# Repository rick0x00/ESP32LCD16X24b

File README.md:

# ESP32 LCD 16X2 4bits

Functional way to connect ESP32 to 16x2 LCD without I2C module, using 4-bit communication.

Here is where the [code](https://github.com/silvajhb/ESP32LCD16X24b/blob/master/SOFTWARE/VSCode/ESP32LCD16X24b/src/main.cpp) stretch you should pay attention to as well as make the [correct connections](https://github.com/silvajhb/ESP32LCD16X24b/blob/master/HARDWARE/DOCUMENTS/sheet.png) in board.

```cpp
const int rs = 23, rw = 4, en = 22, d4 = 5, d5 = 18, d6 = 19, d7 = 21;
LiquidCrystal lcd(rs, rw, en, d4, d5, d6, d7);

```

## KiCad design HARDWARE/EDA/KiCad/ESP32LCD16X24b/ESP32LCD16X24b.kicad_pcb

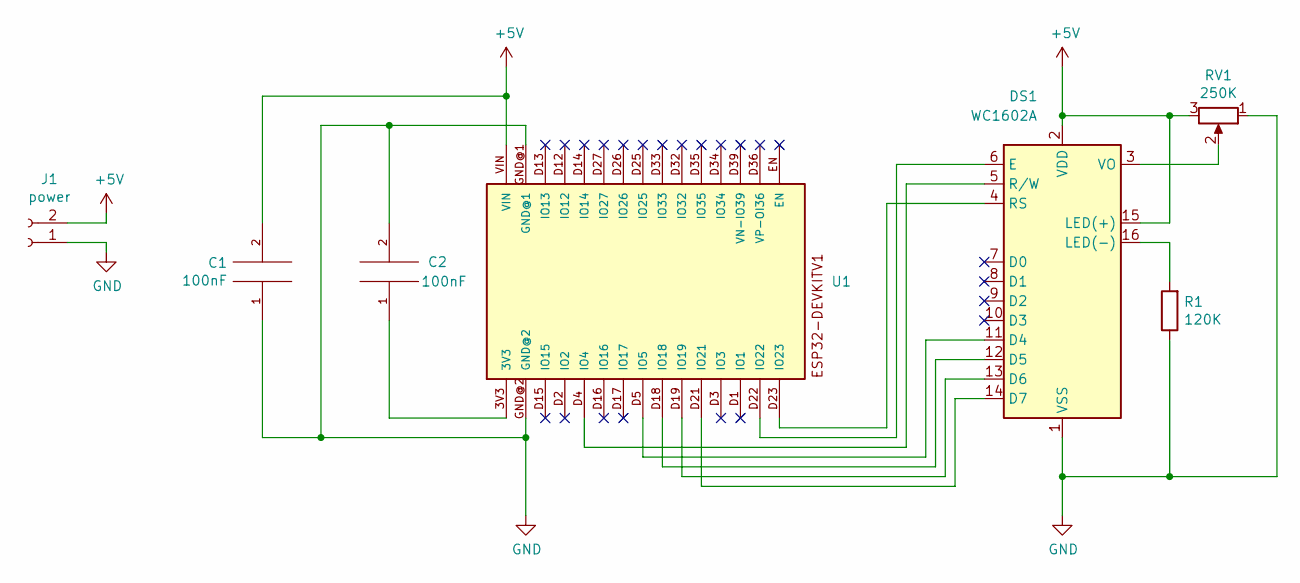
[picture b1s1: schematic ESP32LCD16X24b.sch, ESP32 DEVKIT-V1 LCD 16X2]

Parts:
C1, C2: 100nF; C_Rect_L7.0mm_W2.5mm_P5.00mm
DS1: WC1602A
J1: power; PinSocket_1x02_P2.00mm_Vertical
R1: 120K; R_Axial_DIN0204_L3.6mm_D1.6mm_P5.08mm_Horizontal
RV1: 250K; Potentiometer_Bourns_3266Y_Vertical
U1: ESP32DEVKITV1; ESP32-DEVKITV1

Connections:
+5V: C1.2, DS1.2 (VDD), DS1.15 (LED(+)), J1.2, RV1.3, U1.VIN
GND: C1.1, C2.2, DS1.1 (VSS), J1.1, R1.1, RV1.1, U1.GND@1, U1.GND@2
unnamed: C2.1, U1.3V3
unnamed: DS1.3 (VO), RV1.2
unnamed: DS1.4 (RS), U1.D23 (IO23)
unnamed: DS1.5 (R/W), U1.D4 (IO4)
unnamed: DS1.6 (E), U1.D22 (IO22)
unnamed: DS1.11 (D4), U1.D5 (IO5)
unnamed: DS1.12 (D5), U1.D18 (IO18)
unnamed: DS1.13 (D6), U1.D19 (IO19)
unnamed: DS1.14 (D7), U1.D21 (IO21)
unnamed: DS1.16 (LED(-)), R1.2

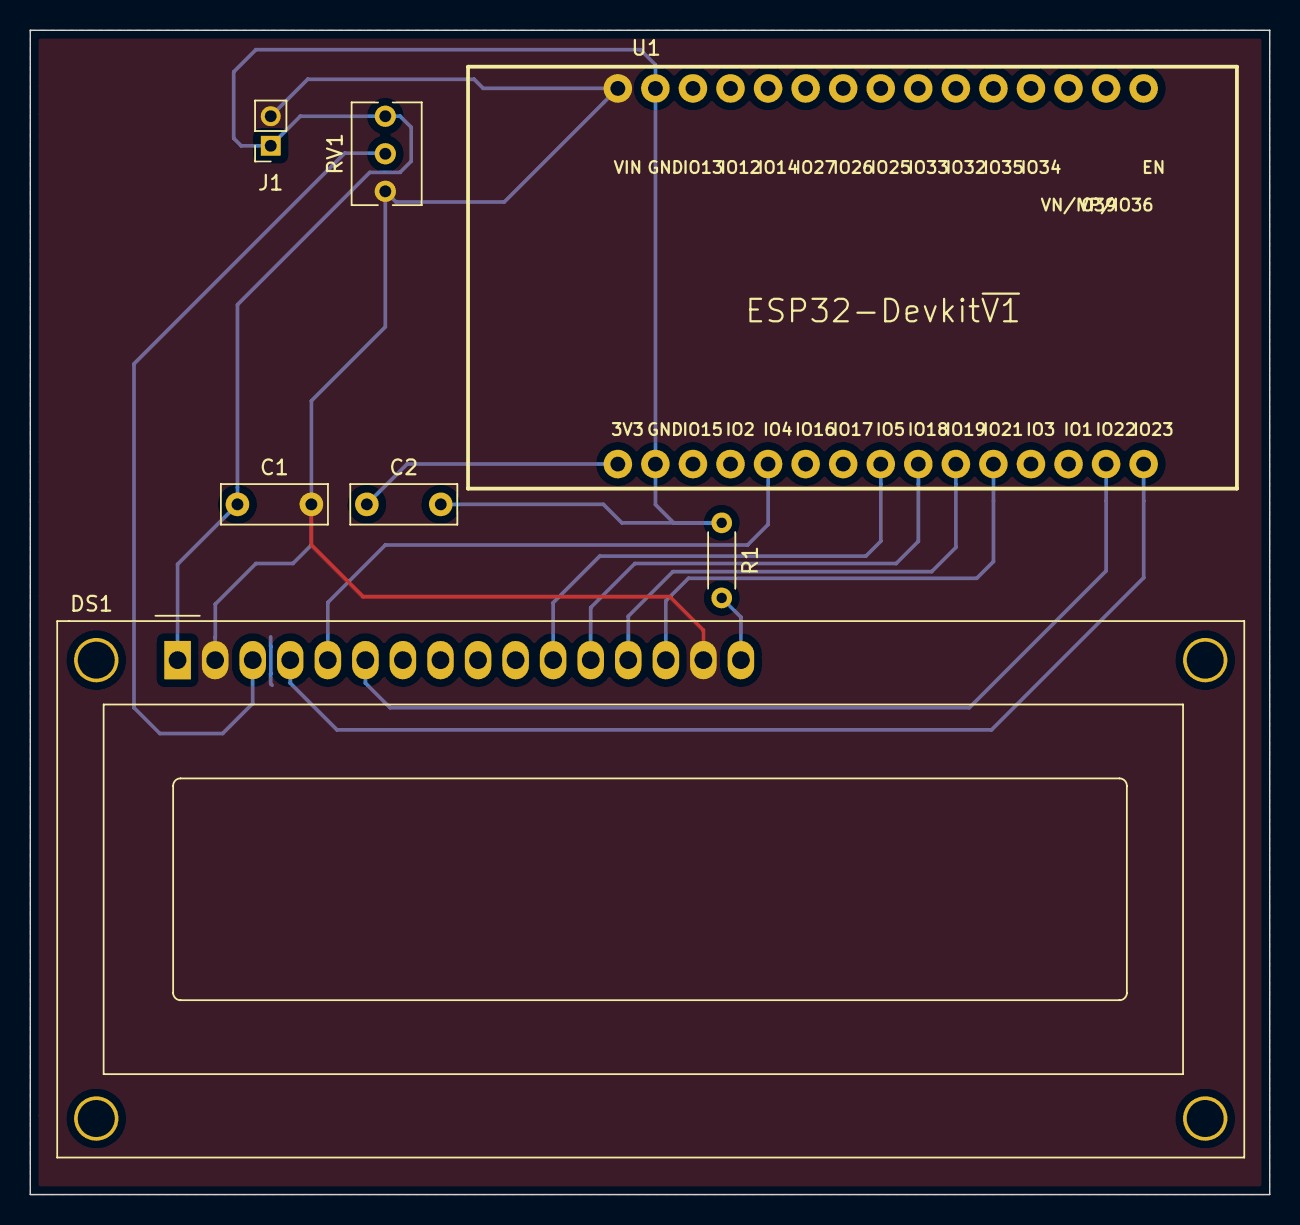
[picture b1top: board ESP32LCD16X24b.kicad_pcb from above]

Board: 2 copper layers, 83.8 x 78.7 mm, 7 parts (0 on the bottom side), 12 nets.

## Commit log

2021-09-23 add files]
2021-09-23 Add pictures
2021-09-23 remove files
2021-09-23 adjust esp32
